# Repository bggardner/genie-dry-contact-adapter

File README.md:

# genie-dry-contact-adapter
Push-Button Adapter for Series III Compatible Genie Garage Door Openers

KiCAD project for a clone of the [Genie Series III Dry Contact Adapter](https://store.geniecompany.com/products/series-iii-dry-contact-adapter-switch)

# Background
After purchasing a Wifi controller for my garage door opener, I realized that my opener did not have a standard push-button ("dry contact") input.
I investigated how my existing [wall console](https://store.geniecompany.com/products/copy-of-wall-console-for-series-ii-product) operated and discovered that it provided three different signals depending on the button that was pushed (DOOR, LIGHT, or LOCK).
The opener provides a soft ~15V to the wall console, and the wall console shorts this signal at a low duty cycle (~10%).  The approximate frequency for each button is as follows:
* DOOR: 16kHz
* LIGHT: 8kHz
* LOCK: 4kHz

The opener detects the frequency of the short and is able to determine which button is pressed.
I was only interested in the DOOR signal, so I simplified the circuit, but a full schematic of the wall console is provided for convenience.
I also discovered that the wall console itself was a dry contact adapter, as it had two-through hole pads in the circuit board that were in parallel with the DOOR button.

# Fabrication
While I initially breadboarded the circuit, I wanted a PCB.
Using [JLCPCB](https://jlcpcb.com), I was able to get five populated/assembled boards delivered for less than $20, not including the [screw terminals](https://www.amazon.com/gp/product/B07H5G7GC6), which I installed myself.
That is much less than a single ~$50 adapter (or ~$30 wall console) sold by Genie, especially given that I have two garage doors.

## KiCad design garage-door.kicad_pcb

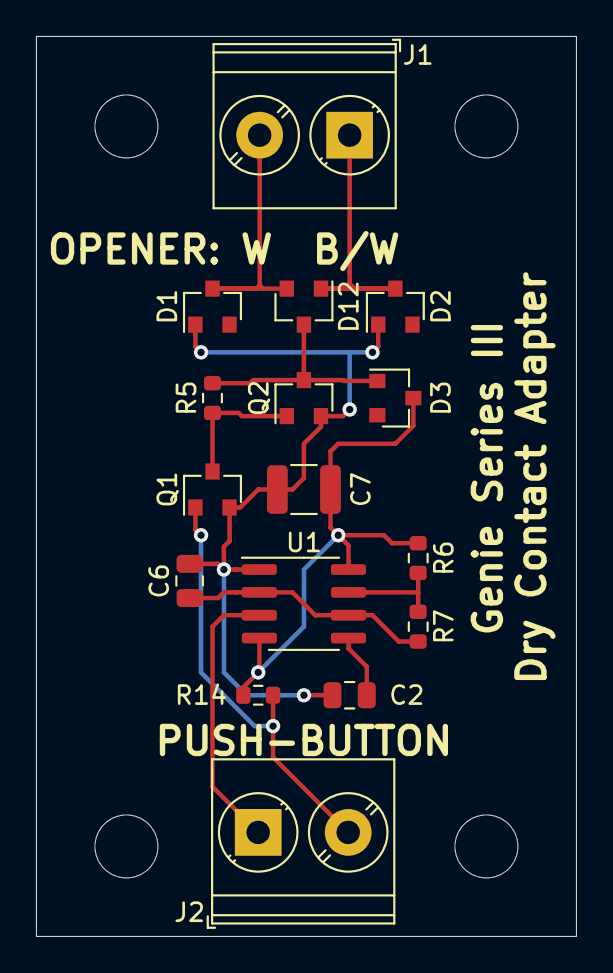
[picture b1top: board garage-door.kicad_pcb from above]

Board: 2 copper layers, 30.0 x 50.0 mm, 20 parts (0 on the bottom side), 11 nets.

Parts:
C2: 0.1uF; C_0805_2012Metric
C6: 1nF; C_0805_2012Metric
C7: 10uF; C_1210_3225Metric
D1, D2, D3, D12: BAT54C; SOT-23
H1, H2, H3, H4: MountingHole; MountingHole_3.5mm
J1: OPENER; TerminalBlock_Phoenix_PT-1,5-2-5.0-H_1x02_P5.00mm_Horizontal
J2: REMOTE; TerminalBlock_Phoenix_PT-1,5-2-5.0-H_1x02_P5.00mm_Horizontal
Q1, Q2: 2N7002; SOT-23
R5: 1.5k; R_0603_1608Metric
R6: 68k; R_0603_1608Metric
R7: 10k; R_0603_1608Metric
R14: 56k; R_0603_1608Metric
U1: NE555DR; SOIC-8_3.9x4.9mm_P1.27mm

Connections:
GND: C2.2, C6.2, C7.1, D1.1, D2.1, Q1.2, Q2.2, U1.1
unnamed: C2.1, U1.5
unnamed: C6.1, R7.2, U1.2, U1.6
unnamed: C7.2, D3.3, R6.1, R14.1, U1.4, U1.8
unnamed: D1.3, D12.2, J1.2
unnamed: D2.3, D12.1, J1.1
unnamed: D3.1, D12.3, Q2.3, R5.2
unnamed: J2.1, U1.3
unnamed: J2.2, Q1.1, R14.2
unnamed: Q1.3, Q2.1, R5.1
unnamed: R6.2, R7.1, U1.7

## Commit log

2022-01-10 Initial load
